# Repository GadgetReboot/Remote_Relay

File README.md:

# Remote_Relay
Remotely control a relay over WiFi or UART pins (use UART with a TTL to RS485 or Bluetooth module etc)
<br><br>
<br><br>

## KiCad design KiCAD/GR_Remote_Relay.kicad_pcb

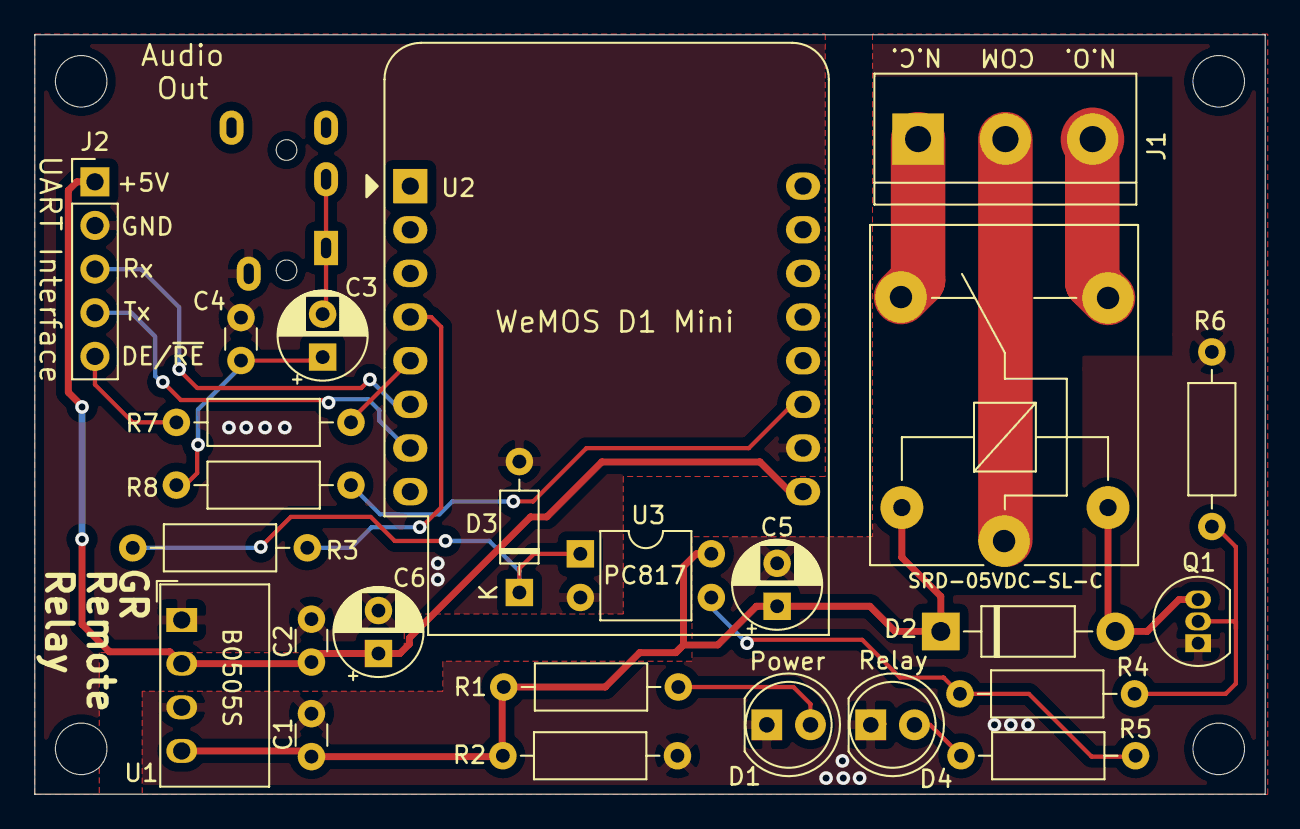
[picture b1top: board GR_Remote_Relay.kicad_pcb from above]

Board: 2 copper layers, 71.6 x 44.2 mm, 30 parts (1 on the bottom side), 21 nets.

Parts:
C1, C2: 100nF; C_Disc_D3.0mm_W1.6mm_P2.50mm
C3, C5, C6: 10uF; CP_Radial_D5.0mm_P2.50mm
C4: 10nF; C_Disc_D3.0mm_W1.6mm_P2.50mm
D1, D4: LED_Small_ALT; LED_D5.0mm
D2: 1N4001; D_DO-41_SOD81_P10.16mm_Horizontal
D3: 1N4148; D_DO-35_SOD27_P7.62mm_Horizontal
J1: Screw_Terminal_01x03; TerminalBlock_bornier-3_P5.08mm
J2: Conn_01x05; PinHeader_1x05_P2.54mm_Vertical
J3: 3.5mm Jack PJ320E; Jack_3.5mm_PJ320E_Horizontal
K1: SRD-05VDC-SL-C; Relay_SPDT_SANYOU_SRD_Series_Form_C
MH1, MH2, MH3, MH4: MountingHole; MountingHole_3mm
Q1: 2N3904; TO-92_Inline
R1, R2, R4, R5, R7, R8: 1K; R_Axial_DIN0207_L6.3mm_D2.5mm_P10.16mm_Horizontal
R3: 470r; R_Axial_DIN0207_L6.3mm_D2.5mm_P10.16mm_Horizontal
R6: 100K; R_Axial_DIN0207_L6.3mm_D2.5mm_P10.16mm_Horizontal
U1: B0505S; Converter_DCDC_muRata_CRE1xxxxxx3C_THT
U2: WeMos_D1_mini; WEMOS_D1_mini_light
U3: PC817; DIP-4_W7.62mm

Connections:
+5V: C1.1, C5.1, D2.1, K1.5, R1.2, R2.2, U1.4, U3.4
+5VD: C2.1, C6.1, J2.1, U1.2, U2.9
/Audio_Out: R8.1, U2.11
/DE_~RE: R7.1, U2.5
/Relay: R4.2, R5.2, U3.3
/Relay_Ctrl: R3.2, U2.4
/RxD: J2.3, U2.6
/TxD: J2.4, U2.7
GND: C1.2, C5.2, D1.1, D4.1, Q1.1, R2.1, R6.1, U1.3
GNDREF: C2.2, C4.2, C6.2, D3.2, J2.2, J3.S, U1.1, U2.10, U3.2
unnamed: C3.1, C4.1, R8.2
unnamed: C3.2, J3.R1, J3.T
unnamed: D1.2, R1.1
unnamed: D2.2, K1.2, Q1.3
unnamed: D3.1, R3.1, U3.1
unnamed: D4.2, R5.1
unnamed: J1.1, K1.4
unnamed: J1.2, K1.1
unnamed: J1.3, K1.3
unnamed: J2.5, R7.2
unnamed: Q1.2, R4.1, R6.2
